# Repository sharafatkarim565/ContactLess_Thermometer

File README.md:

# ContactLess_Thermometer
it's a digital thermometer. that has been built using PCB and programmed on Arduino IDE

#TOP VIEW 

#BOTTOM VIEW

https://github.com/sharafatkarim565/ContactLess_Thermometer/assets/169882984/3d6ccfaf-87c9-4bda-ab52-5931ed5f231a

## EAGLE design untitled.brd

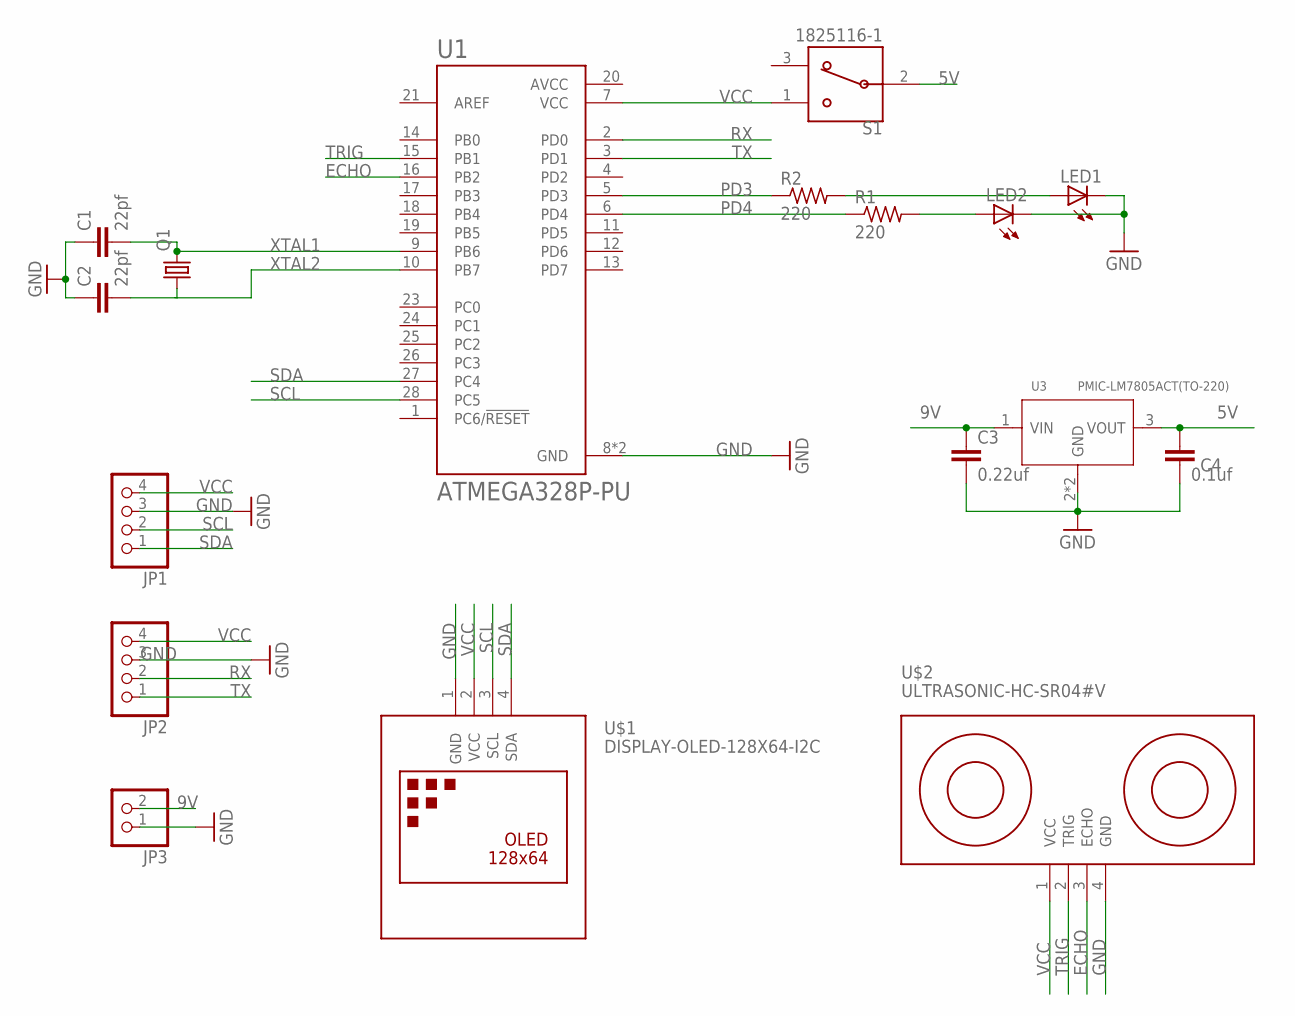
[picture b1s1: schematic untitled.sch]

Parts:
C1, C2: 22pf; C2.5-2
C3: 0.22uf; C2.5-2
C4: 0.1uf; C2.5-2
JP1, JP2: HEADER-1X4; 1X04_OVAL
JP3: HEADER-1X2; 1X02_OVAL
LED1, LED2: LED3MM
Q1: CRYSTALHC49S; HC49/S
R1, R2: 220; 0204/5
S1: 1825116-1; SW_1825116-1
U1: ATMEGA328P-PU; DIP794W46P254L2967H457Q28B
U3: PMIC-LM7805ACT(TO-220); TO-220
U$1: DISPLAY-OLED-128X64-I2C
U$2: ULTRASONIC-HC-SR04#V

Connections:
5V: C4.1, S1.2, U3.3 (VOUT)
9V: C3.1, JP3.2, U3.1 (VIN)
AVCC: U1.20 (AVCC)
ECHO: U1.16 (PB2), U$2.3 (ECHO)
GND: C1.1, C2.1, C3.2, C4.2, JP1.3, JP2.3, JP3.1, LED1.K (C), LED2.K (C), U1.8 (GND), U1.22 (GND), U3.2 (GND), U3.HEAT (GND), U$1.1 (GND), U$2.4 (GND)
unnamed: LED1.A, R2.2
unnamed: LED2.A, R1.2
PD3: R2.1, U1.5 (PD3)
PD4: R1.1, U1.6 (PD4)
RX: JP2.2, U1.2 (PD0)
SCL: JP1.2, U1.28 (PC5), U$1.3 (SCL)
SDA: JP1.1, U1.27 (PC4), U$1.4 (SDA)
TRIG: U1.15 (PB1), U$2.2 (TRIG)
TX: JP2.1, U1.3 (PD1)
VCC: JP1.4, JP2.4, S1.1, U1.7 (VCC), U$1.2 (VCC), U$2.1 (VCC)
XTAL1: C1.2, Q1.2, U1.9 (PB6)
XTAL2: C2.2, Q1.1, U1.10 (PB7)

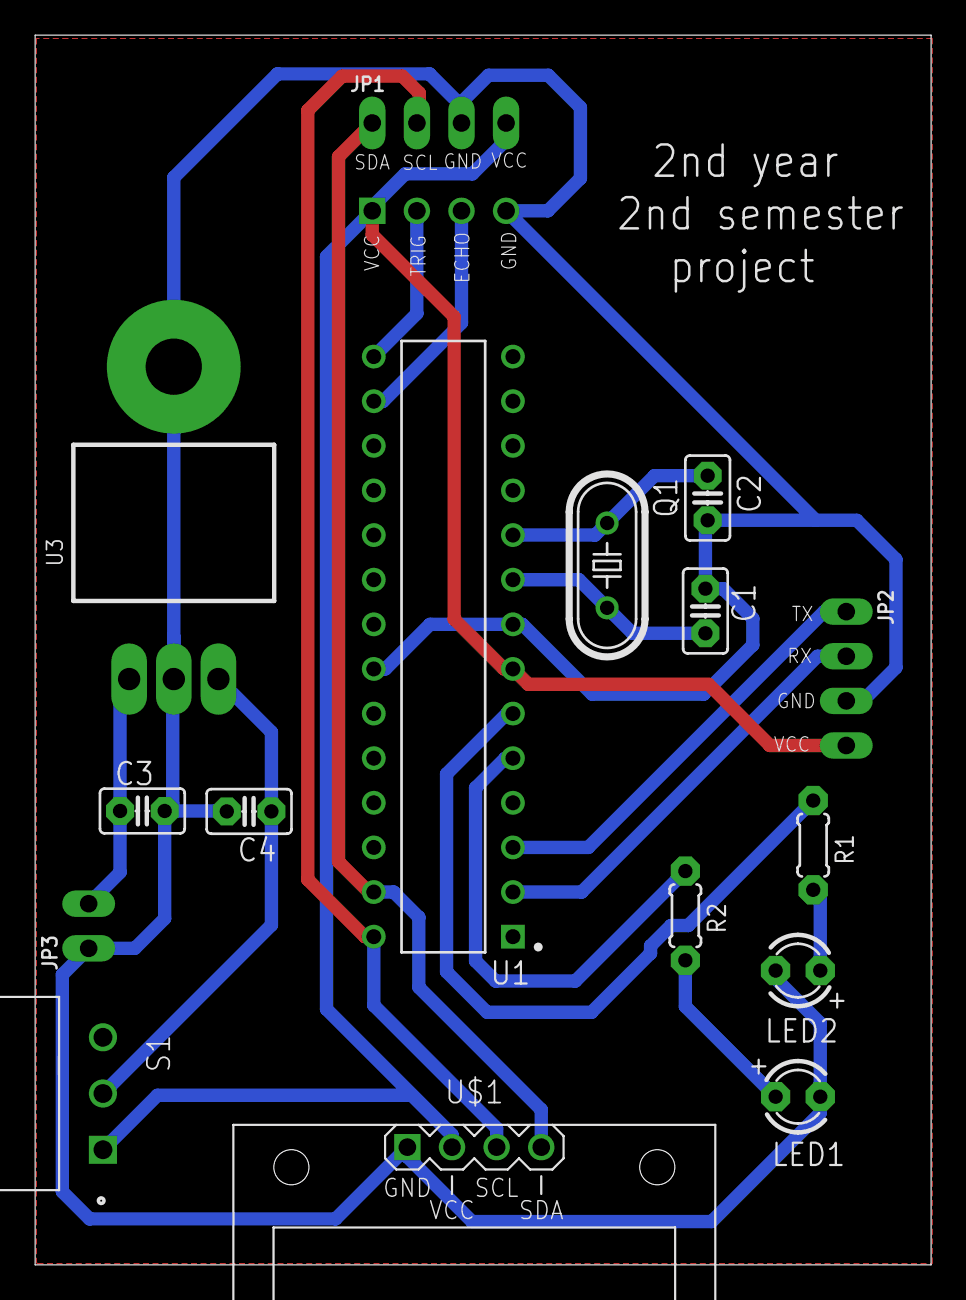
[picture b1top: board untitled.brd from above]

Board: 2 copper layers, 51.0 x 70.0 mm, 17 parts (1 on the bottom side), 16 nets.

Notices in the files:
parts and their libraries:
diy-modules: Released under the Creative Commons Attribution 4.0 International License: http://creativecommons.org/licenses/by/4.0
microbuilder: This work is placed in the public domain, and may be freely used for commercial and non-commercial work with the following conditions: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
